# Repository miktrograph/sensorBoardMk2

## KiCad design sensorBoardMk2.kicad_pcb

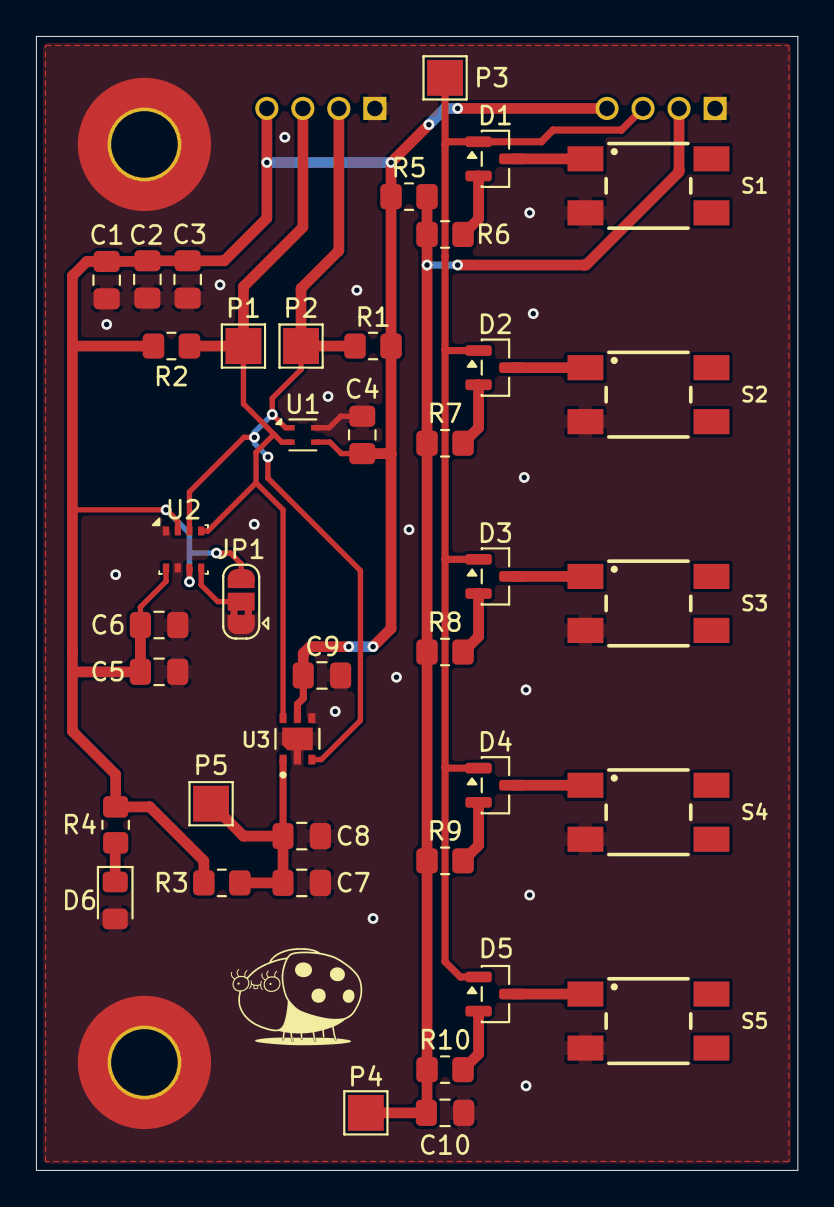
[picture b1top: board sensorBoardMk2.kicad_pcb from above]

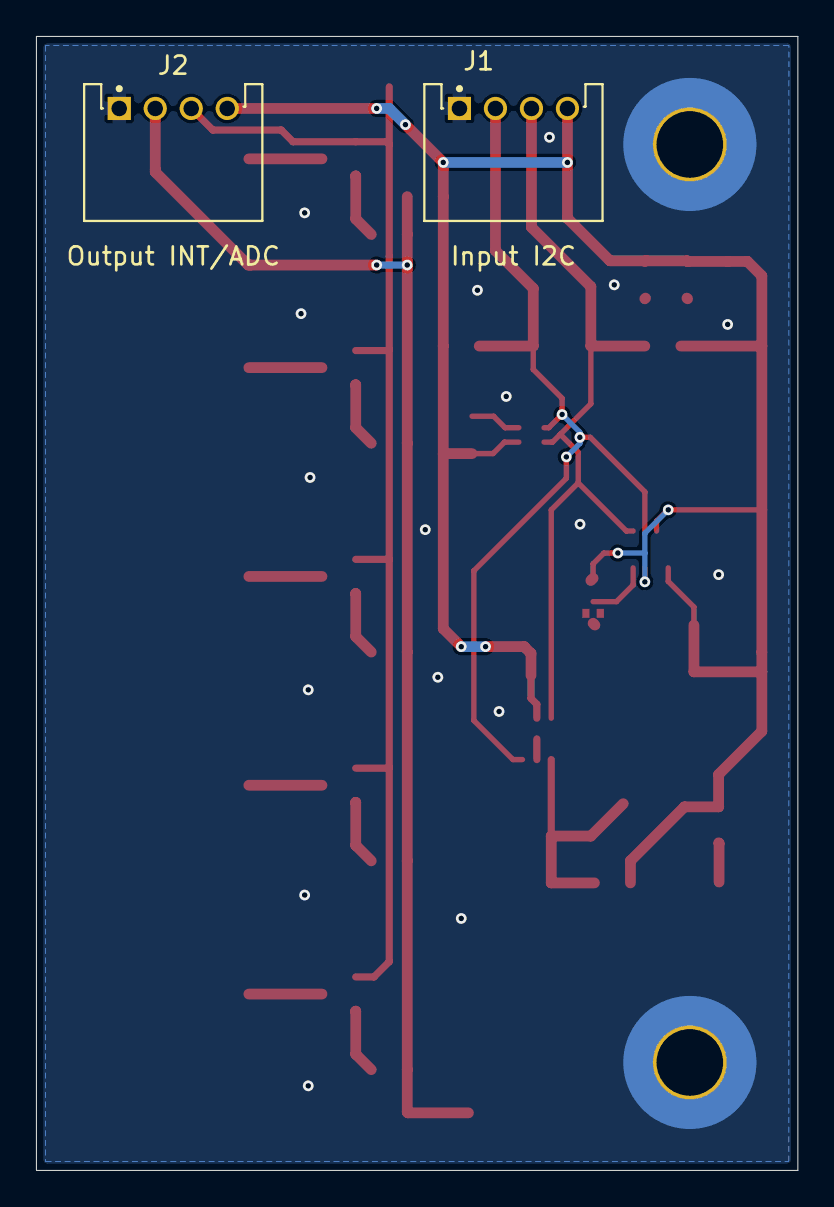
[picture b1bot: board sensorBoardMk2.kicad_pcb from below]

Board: 2 copper layers, 42.3 x 63.0 mm, 44 parts (2 on the bottom side), 19 nets.

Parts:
C1, C2, C3: 10uF; C_0805_2012Metric_Pad1.18x1.45mm_HandSolder
C4, C5, C6, C8, C10: 100nF; C_0805_2012Metric_Pad1.18x1.45mm_HandSolder
C7, C9: 1uF; C_0805_2012Metric_Pad1.18x1.45mm_HandSolder
D1, D2, D3, D4, D5: BAV70; SOT-23
D6: LED_BLUE; LED_0805_2012Metric_Pad1.15x1.40mm_HandSolder
J1, J2: S4B-PH-K-S__LF__SN_; JST_S4B-PH-K-S_LF__SN_
JP1: SolderJumper_3_Bridged12; SolderJumper-3_P1.3mm_Bridged2Bar12_RoundedPad1.0x1.5mm
MountingHoleBottom: MountingHole_3.7mm_Pad_TopBottom
MountingHoleTop: MountingHole_3.7mm_Pad_TopBottom
P1, P2, P3, P4, P5: TP; TestPoint_Pad_2.0x2.0mm
R1, R2, R7: 5.6k; R_0805_2012Metric_Pad1.20x1.40mm_HandSolder
R3: 4.7; R_0805_2012Metric_Pad1.20x1.40mm_HandSolder
R4: 120; R_0805_2012Metric_Pad1.20x1.40mm_HandSolder
R5: 100k; R_0805_2012Metric_Pad1.20x1.40mm_HandSolder
R6: 2.7k; R_0805_2012Metric_Pad1.20x1.40mm_HandSolder
R8: 12k; R_0805_2012Metric_Pad1.20x1.40mm_HandSolder
R9: 22k; R_0805_2012Metric_Pad1.20x1.40mm_HandSolder
R10: 56k; R_0805_2012Metric_Pad1.20x1.40mm_HandSolder
S1, S2, S3, S4, S5: 430181038816
U1: SHT45; Sensirion_DFN-4_1.5x1.5mm_P0.8mm_SHT4x_NoCentralPad
U2: BME280; Bosch_LGA-8_2.5x2.5mm_P0.65mm_ClockwisePinNumbering
U3: SGP40-D-R4; XCDR_SGP40-D-R4

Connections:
+3.3V: C1.1, C2.1, C3.1, C4.1, C5.1, C6.1, C9.1, J1.4, J2.4, JP1.3 (B), R1.1, R2.1, R3.1, R4.1, R5.1, U1.3 (VDD), U2.2 (CSB), U2.6 (VDDIO), U2.8 (VDD), U3.5 (VDDH)
/ADC: C10.1, J2.2, P4.1, R5.2, R6.1, R7.1, R8.1, R9.1, R10.1
/INT: D1.1 (A), D2.1 (A), D3.1 (A), D4.1 (A), D5.1 (A), J2.3, P3.1
/SCL: J1.3, P1.1, R2.2, U1.2 (SCL), U2.4 (SCK), U3.6 (SCL)
/SDA: J1.2, P2.1, R1.2, U1.1 (SDA), U2.3 (SDI), U3.3 (SDA)
GND: C1.2, C2.2, C3.2, C4.2, C5.2, C6.2, C7.2, C8.2, C9.2, C10.2, D6.2 (K), J1.1, J2.1, JP1.1 (A), MountingHoleBottom.1, MountingHoleTop.1, S1.3, S2.3, S3.3, S4.3, S5.3, U1.4 (VSS), U2.1 (GND), U2.7 (GND), U3.2 (VSS), U3.4 (N/A), U3.7 (EXP)
unnamed: D1.2 (A), R6.2
unnamed: D1.3 (K), S1.1
unnamed: D2.2 (A), R7.2
unnamed: D2.3 (K), S2.1
unnamed: D3.2 (A), R8.2
unnamed: D3.3 (K), S3.1
unnamed: D4.2 (A), R9.2
unnamed: D4.3 (K), S4.1
unnamed: D5.2 (A), R10.2
unnamed: D5.3 (K), S5.1
unnamed: D6.1 (A), R4.2
unnamed: JP1.2 (C), U2.5 (SDO)
unnamed: C7.1, C8.1, P5.1, R3.2, U3.1 (VDD)

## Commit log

2025-11-28 Added KiCad Project and data Sheets of the potential parts been used in the project
2025-12-02 Added latest datasheet for led controller
2025-12-02 Added various parts to schematic and populated it in a first draft
2025-12-02 Renamed some folders
2025-12-04 Completed first version of the schema
2026-01-30 Added additional parts to project
2026-02-02 Updated Schematic: Added always power on
2026-02-03 Reworked schema
2026-02-04 Small changes on the page description
2026-02-13 Updated schema to a much simpler version
2026-03-16 Updated the button layout, added diods to seperate the interrupt line from the adc line
2026-04-23 Updated resistor values for buton detection
2026-05-04 Created pcb from schematic
2026-05-12 Checked footprints of special parts
2026-05-13 Updated schema to latest version
2026-05-19 Updated PCB to look cleaner, improved routing
2026-06-07 Replaced the JST connectors with a THT connector, updated general schematics and checked the pinout on all connectors if they match to the LILYGO board
2026-06-07 Made the damn thing smaller
2026-06-07 Did some improvements based on feedback from lil brother
